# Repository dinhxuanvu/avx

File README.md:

View this project on [CADLAB.io](https://cadlab.io/node/951). 

# avx

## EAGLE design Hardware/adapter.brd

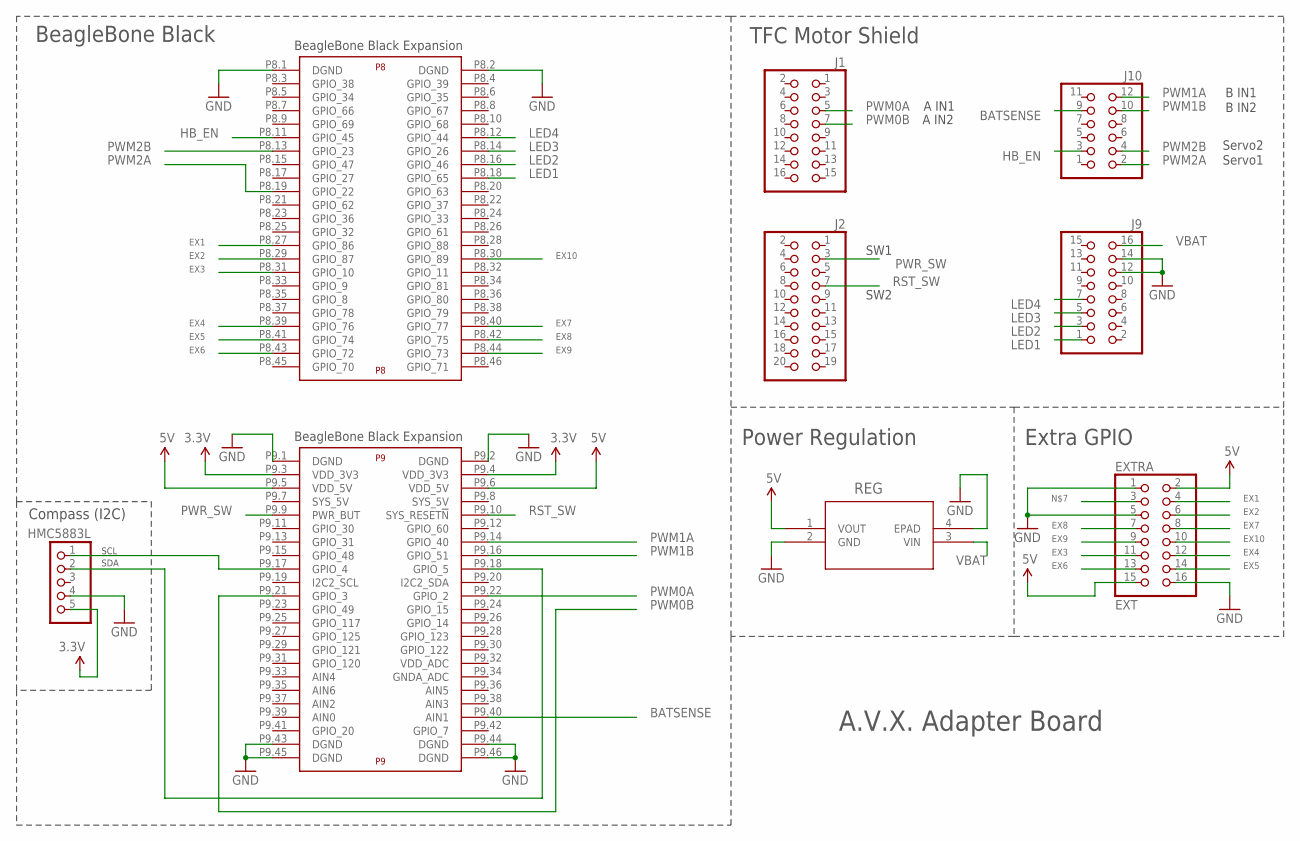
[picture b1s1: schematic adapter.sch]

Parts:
COMPASS: HMC5883L; 1X05
EXTRA: EXT; 2X08
J1, J9: PINHD-2X8; 2X08
J2: PINHD-2X10; 2X10
J10: PINHD-2X6; 2X06
REG: UCC383-5_KTT_3; KTT3_6P22X6P6
U$1: BEAGLE_BONE_BLACK_CAPE

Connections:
3.3V: COMPASS.5, U$1.P9.3 (VDD_3V3), U$1.P9.4 (VDD_3V3)
5V: EXTRA.2, EXTRA.15, REG.1 (VOUT), U$1.P9.5 (VDD_5V), U$1.P9.6 (VDD_5V)
BATSENSE: J10.9, U$1.P9.40 (AIN1)
EX1: EXTRA.4, U$1.P8.27 (GPIO_86)
EX2: EXTRA.6, U$1.P8.29 (GPIO_87)
EX3: EXTRA.11, U$1.P8.31 (GPIO_10)
EX4: EXTRA.12, U$1.P8.39 (GPIO_76)
EX5: EXTRA.14, U$1.P8.41 (GPIO_74)
EX6: EXTRA.13, U$1.P8.43 (GPIO_72)
EX7: EXTRA.8, U$1.P8.40 (GPIO_77)
EX8: EXTRA.7, U$1.P8.42 (GPIO_75)
EX9: EXTRA.9, U$1.P8.44 (GPIO_73)
EX10: EXTRA.10, U$1.P8.30 (GPIO_89)
GND: COMPASS.4, EXTRA.1, EXTRA.5, EXTRA.16, J9.12, J9.14, REG.2 (GND), REG.4 (EPAD), U$1.P8.1 (DGND), U$1.P8.2 (DGND), U$1.P9.1 (DGND), U$1.P9.2 (DGND), U$1.P9.43 (DGND), U$1.P9.44 (DGND), U$1.P9.45 (DGND), U$1.P9.46 (DGND)
HB_EN: J10.3, U$1.P8.11 (GPIO_45)
I2C1_SCL: COMPASS.1, U$1.P9.17 (GPIO_4)
I2C1_SDA: COMPASS.2, U$1.P9.18 (GPIO_5)
LED1: J9.1, U$1.P8.18 (GPIO_65)
LED2: J9.3, U$1.P8.16 (GPIO_46)
LED3: J9.5, U$1.P8.14 (GPIO_26)
LED4: J9.7, U$1.P8.12 (GPIO_44)
PWM0A: J1.5, U$1.P9.22 (GPIO_2)
PWM0B: J1.7, U$1.P9.21 (GPIO_3)
PWM1A: J10.12, U$1.P9.14 (GPIO_40)
PWM1B: J10.10, U$1.P9.16 (GPIO_51)
PWM2A: J10.2, U$1.P8.19 (GPIO_22)
PWM2B: J10.4, U$1.P8.13 (GPIO_23)
PWR_SW: J2.3, U$1.P9.9 (PWR_BUT)
RST_SW: J2.7, U$1.P9.10 (SYS_RESET!N)
VBAT: J9.16, REG.3 (VIN)

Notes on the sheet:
Servo1
Servo2
B IN1
A IN1
B IN2
A IN2
SW1
SW2
BeagleBone Black Expansion
TFC Motor Shield
Power Regulation
BeagleBone Black
A.V.X. Adapter Board
Compass (I2C)
SDA
SCL
Extra GPIO

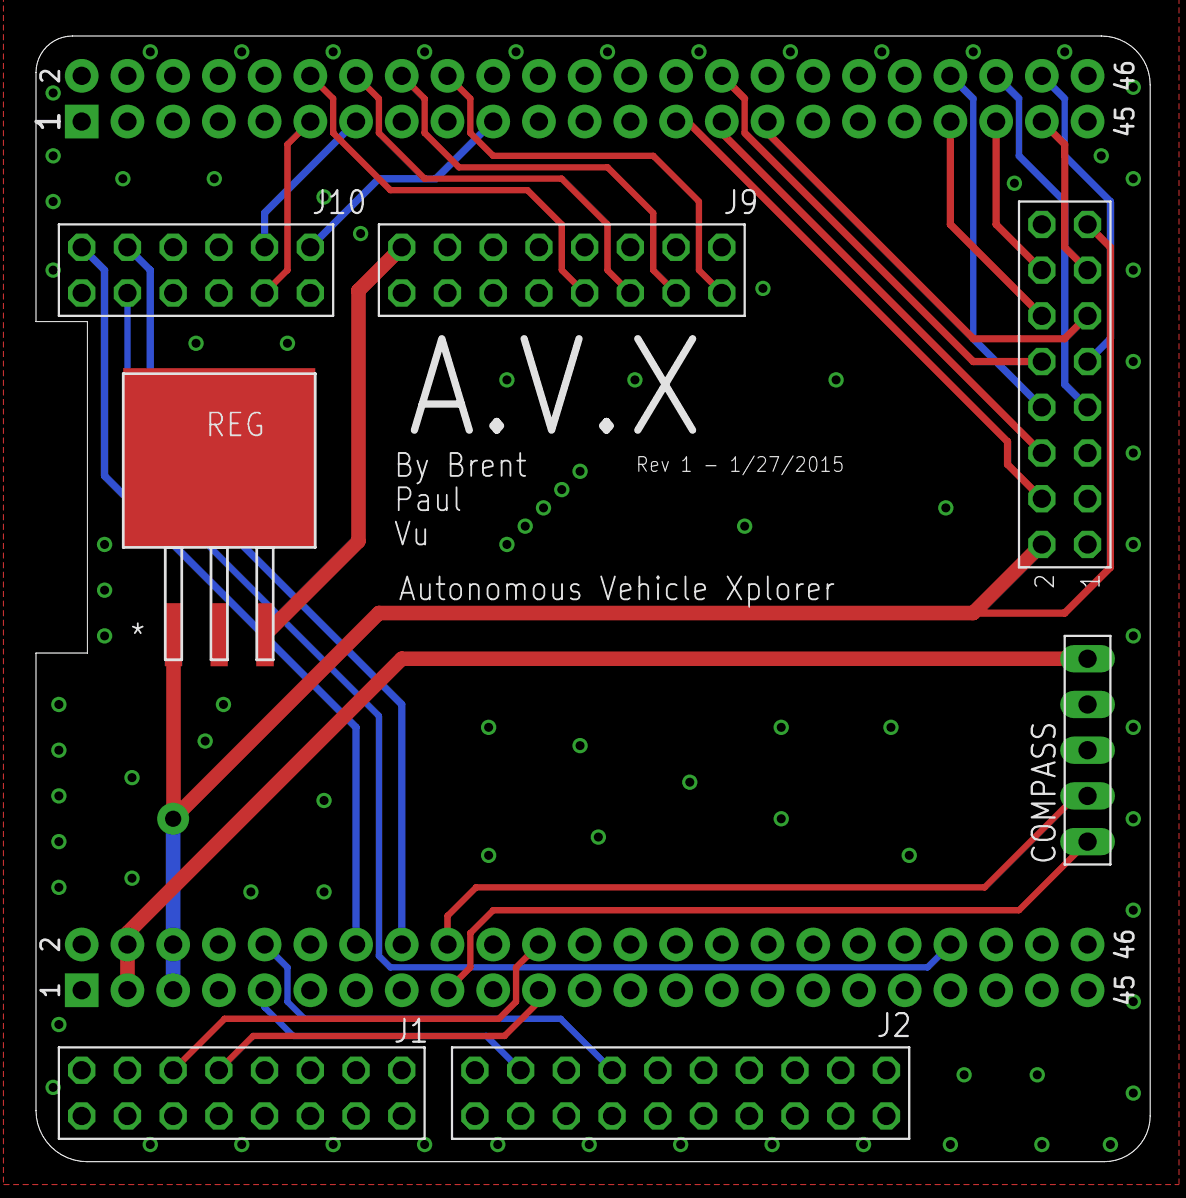
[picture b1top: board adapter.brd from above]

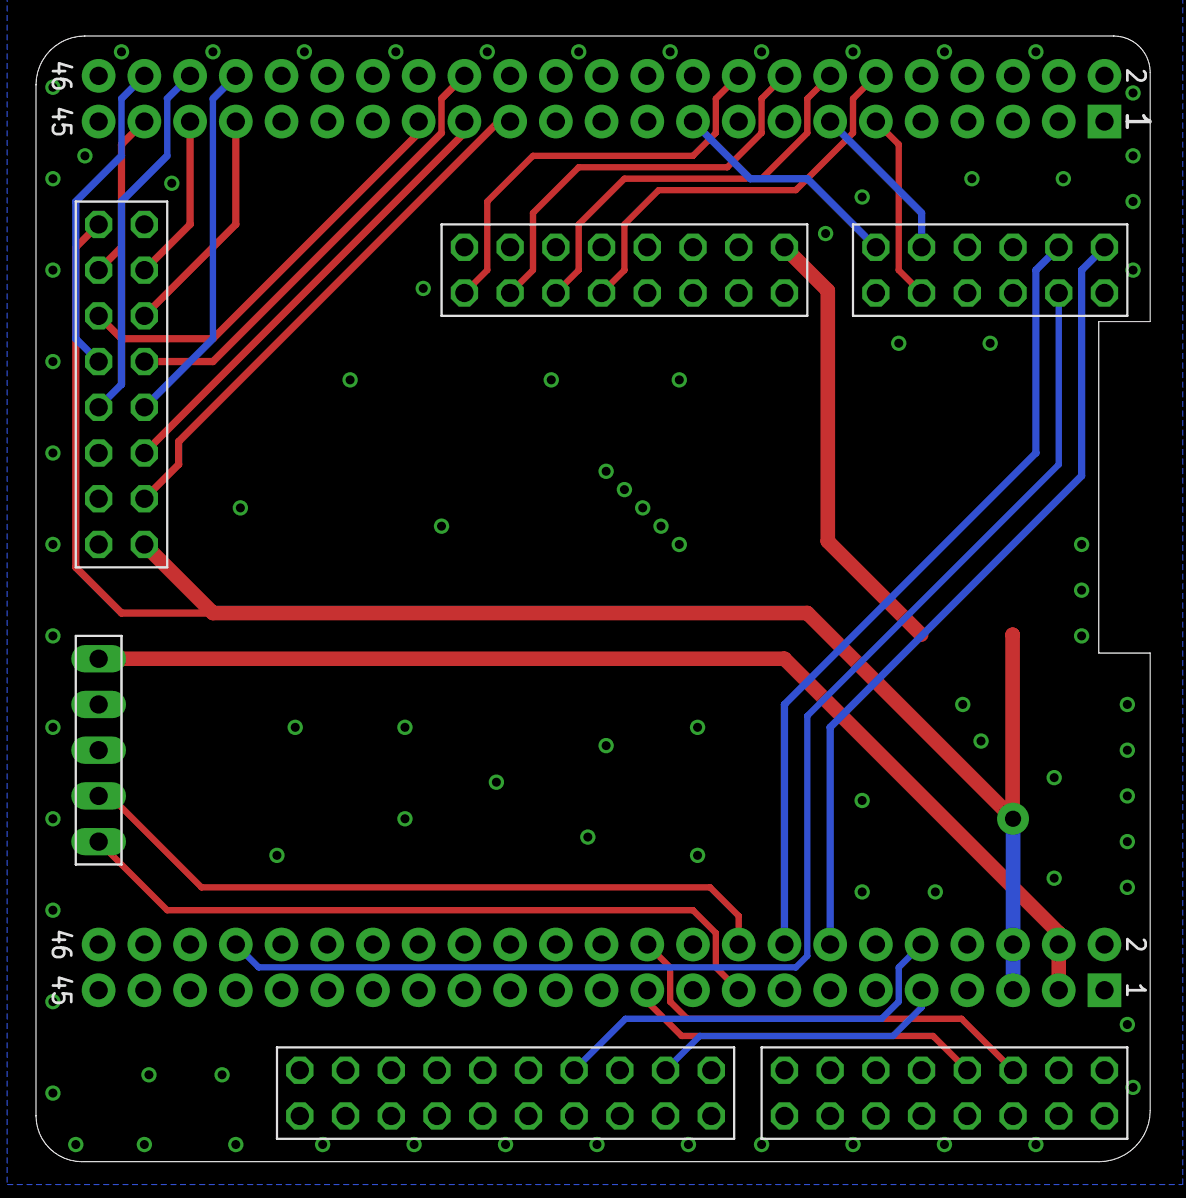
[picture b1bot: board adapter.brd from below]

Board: 2 copper layers, 61.9 x 62.5 mm, 8 parts (4 on the bottom side), 30 nets.

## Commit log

2014-04-23 Added python class for 16x2 LCD display
2014-07-06 Commit Positioning Module files
2014-07-07 Updated startup for i2c and added cron log to git ingore.
2014-07-07 Remote calibration and went with max min calibration. Added python daemon for printing to LCD
2014-09-06 Test
2014-11-12 Added a sample depth/RGB image pair and image processing prototype script in MATLAB.
2014-11-15 Updated image viewing by entire plane subtracting.
2014-11-15 Deleted test and added board schematic and layout.
2014-11-15 Added .gitignore to prototyping too.
2014-11-15 Added GPIO connections for switches and LEDs. Updated routing.
2014-11-15 Updated board outline.
2014-11-15 Added 5V regulator. Fixed J9 flip issue.
2014-11-17 Update schematic to be sectioned off and organized.
2014-11-17 Testing pushing file on Device branch.
2014-11-18 Added GPIO and Image processing modules on BBB with sample applications.
2014-11-18 Deleted test message and merged into remote device
2014-11-18 Updated Simple read to view entire frame and use OpenCV. Makefile updated for CV
2014-11-18 Implemented LED, PWM, servo functions into GPIO module in C.
2014-11-19 Added test module for unit test, integration tests, and eventually acceptance tests.
2014-11-19 Updated GPIO after testing
2014-11-19 Moved overlay directory and added startup scripts for initializing GPIO, PWM
2014-11-19 Updated and testing servo functions
2014-11-19 Converted GPIO module to C++ class using Singleton design pattern.
2014-11-20 Updated GPIO module and compile with C++ implementation. Header, implementation correct. Updated makefile
2014-11-20 Updated PWM for motor control, forward and reverse implemented. Both motor channels verified. Tested enableHBridge
2014-11-20 Renamed test for GPIO test
2014-11-20 Added ImageBufferManager which is used to buffer reading and writing image data between the camera and image processing data. This way they can run independently. New make file for building, and glob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
2014-11-22 Updated header dimensions. Added Extra connector for GPIO.
2014-11-23 Updated board tPlace and bPlace.
2014-11-24 Converted to TI LDO component.
2014-11-24 Added ADC (untested) code and fixed comments/styling
2014-11-24 Added ADC initializatio into GPIO constructor
2014-11-24 Minor fixes to compile code with development libraries only.
2014-11-25 Added installation script for libraries
2014-11-25 Updated test cases for GPIO and Makefile
2014-11-26 Added object (.o) files to gitignore
2014-11-28 Commented makefile and cleaned up includes/targets
2014-12-01 Modified makefile to manually merge the desired dependency format with, new GPIO module target
2014-12-01 Make ImageBufferManager compile. Still has strange errors, and doesn't work yet.
2014-12-04 Added simple timer to measure camera framerate
2014-12-04 Renamed directories and moved unit tests to individual folders
2014-12-04 Fixed makefile to correctly make all targets. All targets compile.
2014-12-04 Added image processor module with basic OpenCV functions. Start of implementation. Updated makefile to compile
2014-12-04 Added boost thread test to test_BufferManager
2014-12-04 Updated image processor tests and makefile. Compiles and runs
2014-12-04 Modified sample images in media folder to contain different objects.
2014-12-04 Updated image processing to do background subtraction and thresholding
2014-12-05 Updated image processor to find distinct image chunks based on min.
2014-12-05 Image processing now finds and draws bounding box on separate obstacles
2014-12-05 Renamed WALLE to AVX on PCB.
2014-12-05 Added 2 and 3 obstacles frames to test. Obstacle detection now draws polygon approx.
2014-12-07 Added thread checks to buffer manager, and verifyed thread safty.
2014-12-08 Added overlapping boxes sample image.
2014-12-08 Added edge detection for overlapping obstacles. Successfully detected 2 overlaps
2014-12-09 Updated makefile to fix lib include issue.
2014-12-09 UPdated makefile for include pkg path for image processor
2014-12-13 Added hazard standard for image processing/path planning interface. Updated Image Processor to parse our hazards
2014-12-16 Fixed frame rate calculation
2014-12-16 UPdated makefile for mac inclusiveness
2015-01-27 Fixed issue with pinout for magnetometer. Updated layout ground plane vias.
2015-01-27 Added text title and updated revision date.
2015-01-27 Updated text size to prevent overflow.
2015-01-30 Code broken, Brent trying to fix it
2015-02-03 Fixed buffer manager. Camera Device went out of scope causing a video stream to fail its read.
2015-02-03 Added macros file for printing debug messages
2015-02-03 Multithreaded and OOPed Camera and ImageProccessor
2015-02-03 Multithreading works with showing image. Data conversion issue to be fixed.
2015-02-03 updated image processor display data conversion. Working version!
2015-02-05 Tuned image processing more. Updated calibration phase.
2015-02-06 Updated image processor for plane calculation with random points.
2015-02-06 Made full speed camera reading and image processing
2015-02-09 Tuning image processing algorithms to detect smaller and further objects.
2015-02-09 Added PathPlanner module and moved global includes around. Set up basic structure for path planning.
2015-02-10 Updated GPIO values to be consistent and all floats.
2015-02-10 Updated includes in image processor
2015-02-10 Added bones of control module.
2015-02-10 Tuned plane finding with more points and updated edge parameters. Works well.
2015-02-10 Fixed segfault when running main program without showing any windows.
2015-02-12 Updated startup with git pull and make play. Added host specific DISPLAY to makefile.
2015-02-12 Added test_GPIO to makefile for bbb
2015-02-12 Fixed startup scripts to run make play and do all overlays
2015-02-13 Updated test_GPIO to only read battery.
2015-02-13 UPdated battery to convert to 0 to 1.0 percent
2015-02-13 Minor edits to GPIO battery level. Perform every loop now.
2015-02-17 Added positioing module
2015-02-19 Update PathPlanner
2015-02-19 Added positioning module to makefile and separated it from PathPlanner. Added test file.
2015-02-19 Added DISPLAY if statements for BBB
2015-02-19 Updated positioning module i2c pointers and HMC.
2015-02-19 Fixed extra includes being in main program, causing it to not compile
2015-02-19 Change Positioning
2015-02-19 Add namespace in Positioning
2015-02-19 Test Positioning
2015-02-19 Test 2
2015-02-19 Add test files to Positioning
2015-02-19 Second Up
2015-02-19 Yes 3
2015-02-19 Yes 4
2015-02-19 Yes 6
2015-02-19 Final Yes
2015-02-19 Fixed make environment variable DISPLAY overwriting the X variable. This stops GTK from getting the current X sesstion
2015-02-19 Un pointered everything
2015-02-19 Fixed Positioing module and tested to be working.
2015-02-26 Updated positioning module for calibration and displacement return
2015-02-26 Updated path planner with separation of local map and best path
2015-02-26 Added hazard struct alternate
2015-02-26 Remove error at top of path planner.
2015-02-26 Updated local mapping and function prototypes.
2015-03-03 Added path planner to main
2015-03-03 Updated control module with PID methods and interface with main/path planning.
2015-03-03 Added include to main
2015-03-03 Updated hazard to not include XY hazard
2015-03-03 Created stub for GPIO without hardware
2015-03-03 Partially done with path planner
2015-03-04 Fixed hazXY compile errors, and added a threshold version of path planning
2015-03-05 Updated scritps and makefile for new beaglebone
2015-03-05 Updated control with get angle callback and turn=angle
2015-03-05 Updated GPIO for update battery exe.
2015-03-05 Updated positioning module includes.
2015-03-05 Finished initial path planning code
2015-03-05 Initial Path Planning Code
2015-03-10 Updated GPIO for physical car settings
2015-03-10 Updated control speed to be linaer
2015-03-13 Improved best path to take into account a linear interpolation of badness from the center of objects
2015-03-31 Changed path planner to read the real heading when on the real device
2015-03-31 Fixed camera settings not being set. Simplified makefile .o files
2015-03-31 Updated Battery sense mode to not throw SIGNALRM
2015-04-02 Temporarly disabled path looking at camera information to test magnetometer
2015-04-02 Updated positiong to read three values and corrected offset calculation
2015-04-02 Added camera back into path planner
2015-04-02 Updated Control by adding PID
2015-04-07 Added kill program to stop motors
2015-04-07 Added ctrl-c handeling to stop the h-bridge. Changed a sign in image processing to flop the image. Added hazardlist printing to the screen
2015-04-07 Greatly improved image processing
2015-04-07 No Timegit add PathPlanner/PathPlanner.cppgit add PathPlanner/PathPlanner.cpp
2015-04-07 No Time
2015-04-07 Running test
2015-04-08 Added stop hazard type
2015-04-08 Minor refactor of path planner. Moved positioning outside of best path
2015-04-08 Updated Kill in makefile to run motor kill before killall
2015-04-08 Fixed path planner seg fault when empty list
2015-04-08 Make reverse change directions
2015-04-08 Update startup makefile
2015-04-08 Updated makefile, startup script, and modified turn direction on reverse
2015-04-09 Removed commented function
2015-04-09 Changed startup script to not stash
2015-04-09 Cleared queue when resetting sum
2015-04-14 Removed extra prints in image process and GPIO. Averaging positioning values
2015-04-16 Major changes to interface between path and control. Updates to positioning calculations
2015-04-16 Added calibration and center finding code to calibrate module
2015-04-18 Updated positioning to use LCD for output. Update python daemon in startup script. Now uses stderr
2015-04-18 Added GPIO calibration circle method. Updated control negative sign. Drives striaght now
2015-04-18 Added camera. Updated weights. Added cautious state. Changed hazard sort.
2015-04-18 Make run now starts avx instead of heading test.
2015-04-18 DOn't car
2015-04-18 Split large walls into smaller rectangles with different distances
2015-04-19 CHanges from car. Thresholds on hazards.
2015-04-21 Updated reverse threshold for detection. Works well around room with no compass
2015-04-21 Debounced mode changes for path planner display to LCD
2015-04-21 Single line output for LCD
2015-04-21 Smoothed out LCD printing. Increased the amount of time in cautious mode.
2018-04-27 Backlink to CADLAB.io has been added.

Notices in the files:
parts and their libraries:
SparkFun-Aesthetics: Licensing: Creative Commons ShareAlike 4.0 International - https://creativecommons.org/licenses/by-sa/4.0
